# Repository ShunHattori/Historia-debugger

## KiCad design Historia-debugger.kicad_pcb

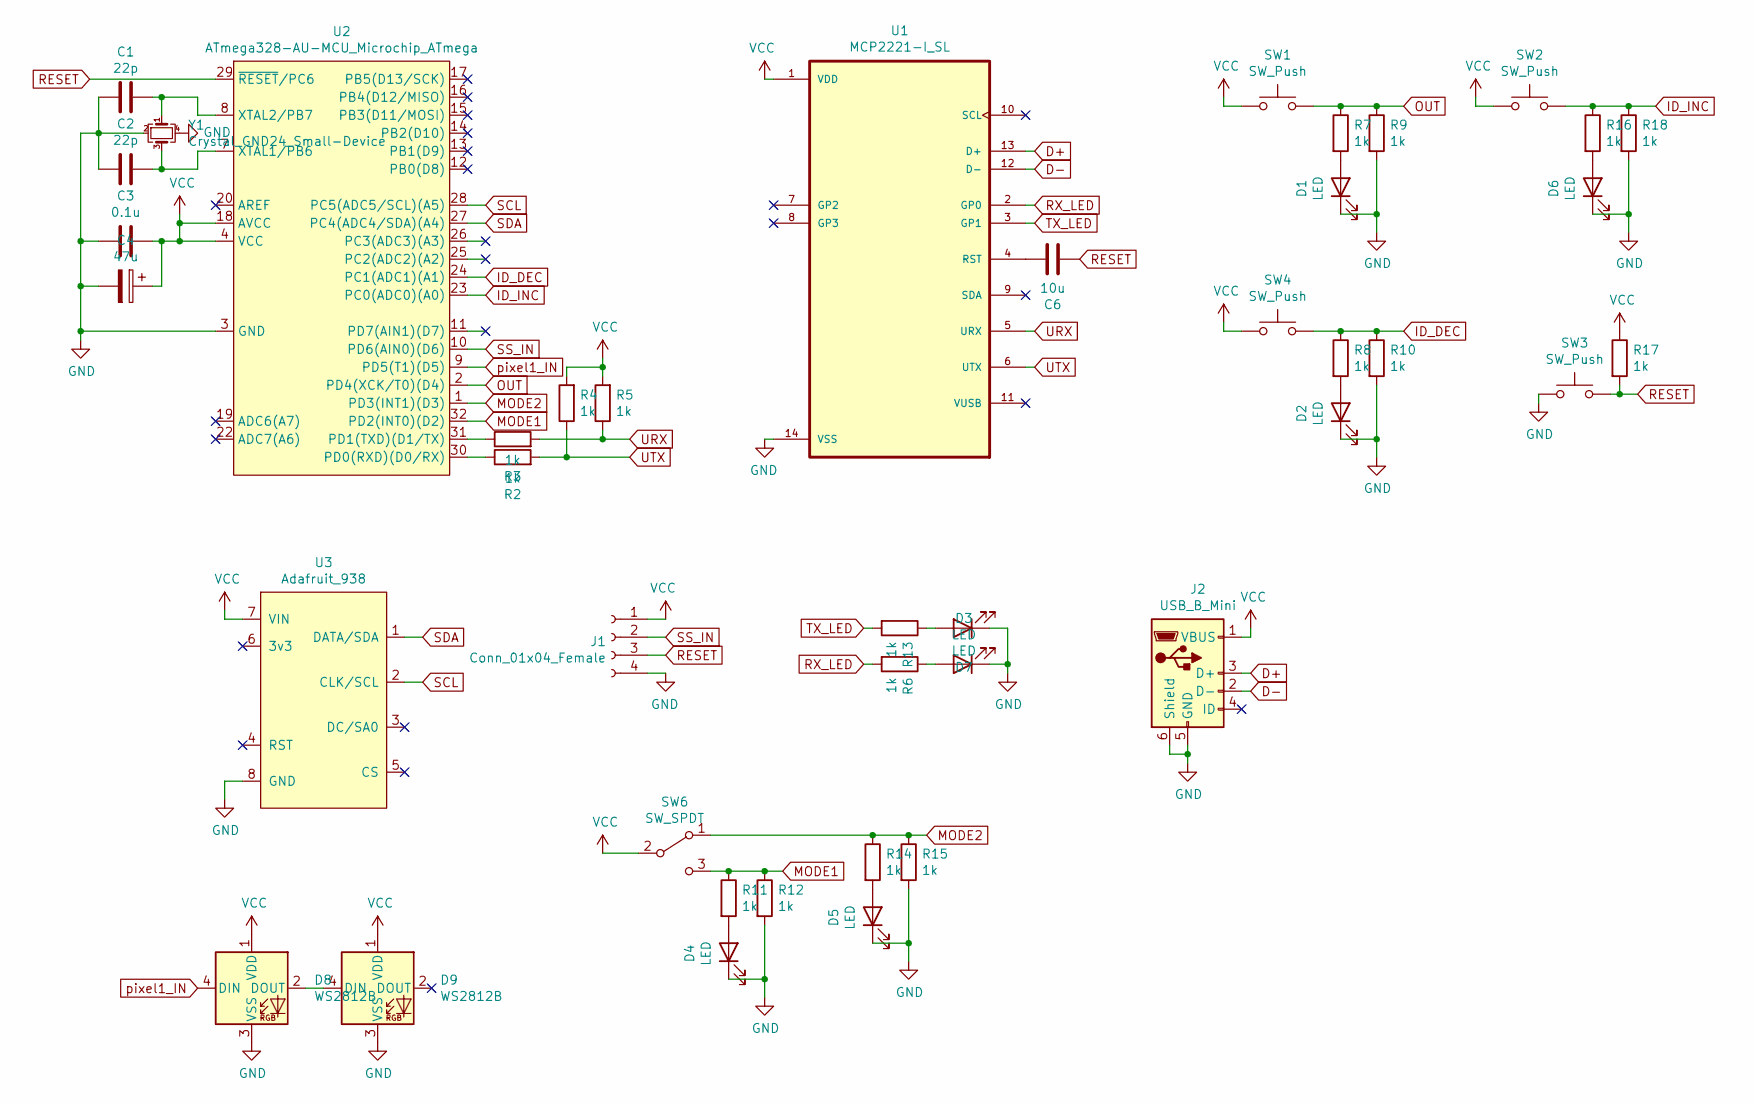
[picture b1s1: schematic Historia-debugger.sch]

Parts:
C1, C2: 22p; C_0603_1608Metric
C3: 0.1u; C_0603_1608Metric
C4: 47u; CP_Elec_6.3x5.4
C6: 10u; C_0603_1608Metric
D1, D2, D3, D4, D5, D6, D7: LED; LED_0603_1608Metric
D8, D9: WS2812B; LED_WS2812B_PLCC4_5.0x5.0mm_P3.2mm
J1: Conn_01x04_Female; JST_XH_S4B-XH-A_1x04_P2.50mm_Horizontal
J2: USB_B_Mini; USB_Mini_B_holes
R2, R3, R4, R5, R6, R7, R8, R9, R10, R11, R12, R13, R14, R15, R16, R17, R18: 1k; R_0603_1608Metric
SW1, SW2, SW3, SW4: SW_Push; SW_PUSH_6mm_H4.3mm
SW6: SW_SPDT; SW_E-Switch_EG1271_DPDT
U1: MCP2221-I_SL; SOIC127P600X175-14N
U2: ATmega328-AU-MCU_Microchip_ATmega; TQFP-32_7x7mm_P0.8mm
U3: Adafruit_938; Adafruit_SSD1306
Y1: Crystal_GND24_Small-Device; Crystal_SMD_SeikoEpson_FA238-4Pin_3.2x2.5mm

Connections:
D+: J2.3 (D+), U1.13 (D+)
D-: J2.2 (D-), U1.12 (D-)
GND: C1.2, C2.2, C3.2, C4.2, D1.1 (K), D2.1 (K), D3.1 (K), D4.1 (K), D5.1 (K), D6.1 (K), D7.1 (K), D8.3 (VSS), D9.3 (VSS), J1.4, J2.5 (GND), J2.6 (Shield), R9.2, R10.2, R12.2, R15.2, R18.2, SW3.1, U1.14 (VSS), U2.3 (GND), U2.5 (GND), U2.21 (GND), U3.8 (GND), Y1.2, Y1.4; also elsewhere on the board
ID_DEC: R8.1, R10.1, SW4.2, U2.24 (PC1(ADC1)(A1))
ID_INC: R16.1, R18.1, SW2.2, U2.23 (PC0(ADC0)(A0))
MODE1: R11.1, R12.1, SW6.3 (C), U2.32 (PD2(INT0)(D2))
MODE2: R14.1, R15.1, SW6.1 (A), U2.1 (PD3(INT1)(D3))
unnamed: C1.1, U2.8 (XTAL2/PB7), Y1.1
unnamed: C2.1, U2.7 (XTAL1/PB6), Y1.3
unnamed: C6.2, U1.4 (RST)
unnamed: D1.2 (A), R7.2
unnamed: D2.2 (A), R8.2
unnamed: D3.2 (A), R6.1
unnamed: D4.2 (A), R11.2
unnamed: D5.2 (A), R14.2
unnamed: D6.2 (A), R16.2
unnamed: D7.2 (A), R13.1
unnamed: D8.2 (DOUT), D9.4 (DIN)
unnamed: R2.1, U2.30 (PD0(RXD)(D0/RX))
unnamed: R3.1, U2.31 (PD1(TXD)(D1/TX))
OUT: R7.1, R9.1, SW1.2, U2.2 (PD4(XCK/T0)(D4))
RESET: C6.1, J1.3, R17.2, SW3.2, U2.29 (~RESET~/PC6)
RX_LED: R6.2, U1.2 (GP0)
SCL: U2.28 (PC5(ADC5/SCL)(A5)), U3.2 (CLK/SCL)
SDA: U2.27 (PC4(ADC4/SDA)(A4)), U3.1 (DATA/SDA)
SS_IN: J1.2, U2.10 (PD6(AIN0)(D6))
TX_LED: R13.2, U1.3 (GP1)
URX: R3.2, R5.1, U1.5 (URX)
UTX: R2.2, R4.1, U1.6 (UTX)
VCC: C3.1, C4.1, D8.1 (VDD), D9.1 (VDD), J1.1, J2.1 (VBUS), R4.2, R5.2, R17.1, SW1.1, SW2.1, SW4.1, SW6.2 (B), U1.1 (VDD), U2.4 (VCC), U2.6 (VCC), U2.18 (AVCC), U3.7 (VIN); also elsewhere on the board
pixel1_IN: D8.4 (DIN), U2.9 (PD5(T1)(D5))

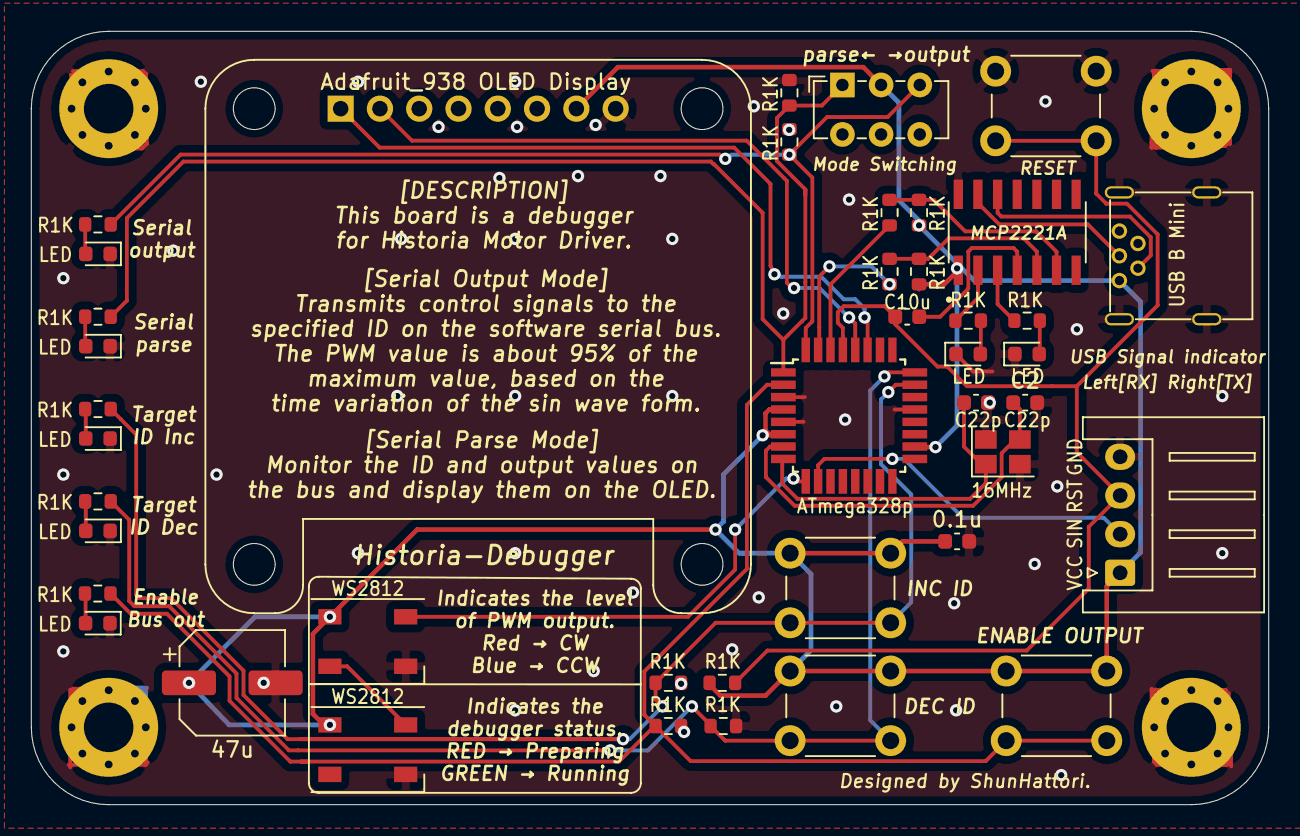
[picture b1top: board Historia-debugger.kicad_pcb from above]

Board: 2 copper layers, 80.0 x 50.0 mm, 42 parts (0 on the bottom side), 31 nets.

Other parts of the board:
0.1u: 0.1u; C_0603_1608Metric
47u: 47u; CP_Elec_6.3x5.4

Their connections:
GND: 0.1u.2, 47u.2; also elsewhere on the board
VCC: 0.1u.1, 47u.1; also elsewhere on the board

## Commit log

2020-12-30 fixed QR CODE silk
2020-12-30 rename PCB name
2021-01-24 add silks and QR
